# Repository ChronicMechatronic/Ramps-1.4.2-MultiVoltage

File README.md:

# Ramps-1.4.2-MultiVoltage

Special version of Ramps 1.4.2 allowing use of multiple power adapters to power a 3D printer.

Contains 5 seperate voltage rails for:
a 19.5V heated bed
a 12V hotend
one separate 12V stepper motor
two steppers running on 24V
one 5V stepper

The fifth stepper motor driver can be set to run off either the 5V, 12V, or 24V rail via 0 ohm links to be soldered on as necessary (add R30 for 5V; R29 for 12V; or R28 for 24V)
If you have a sufficiently powerful power supply the two 12V rails can be combined to run off a single barrel jack by populating R10 and R11 with 0 ohm links.

None of the voltage rails are constrained by anything other than the voltage rating of its capacitor, so repurpose as you please.

For pretty much everything else the standard documentation on https://reprap.org/wiki/RAMPS_1.4 applies

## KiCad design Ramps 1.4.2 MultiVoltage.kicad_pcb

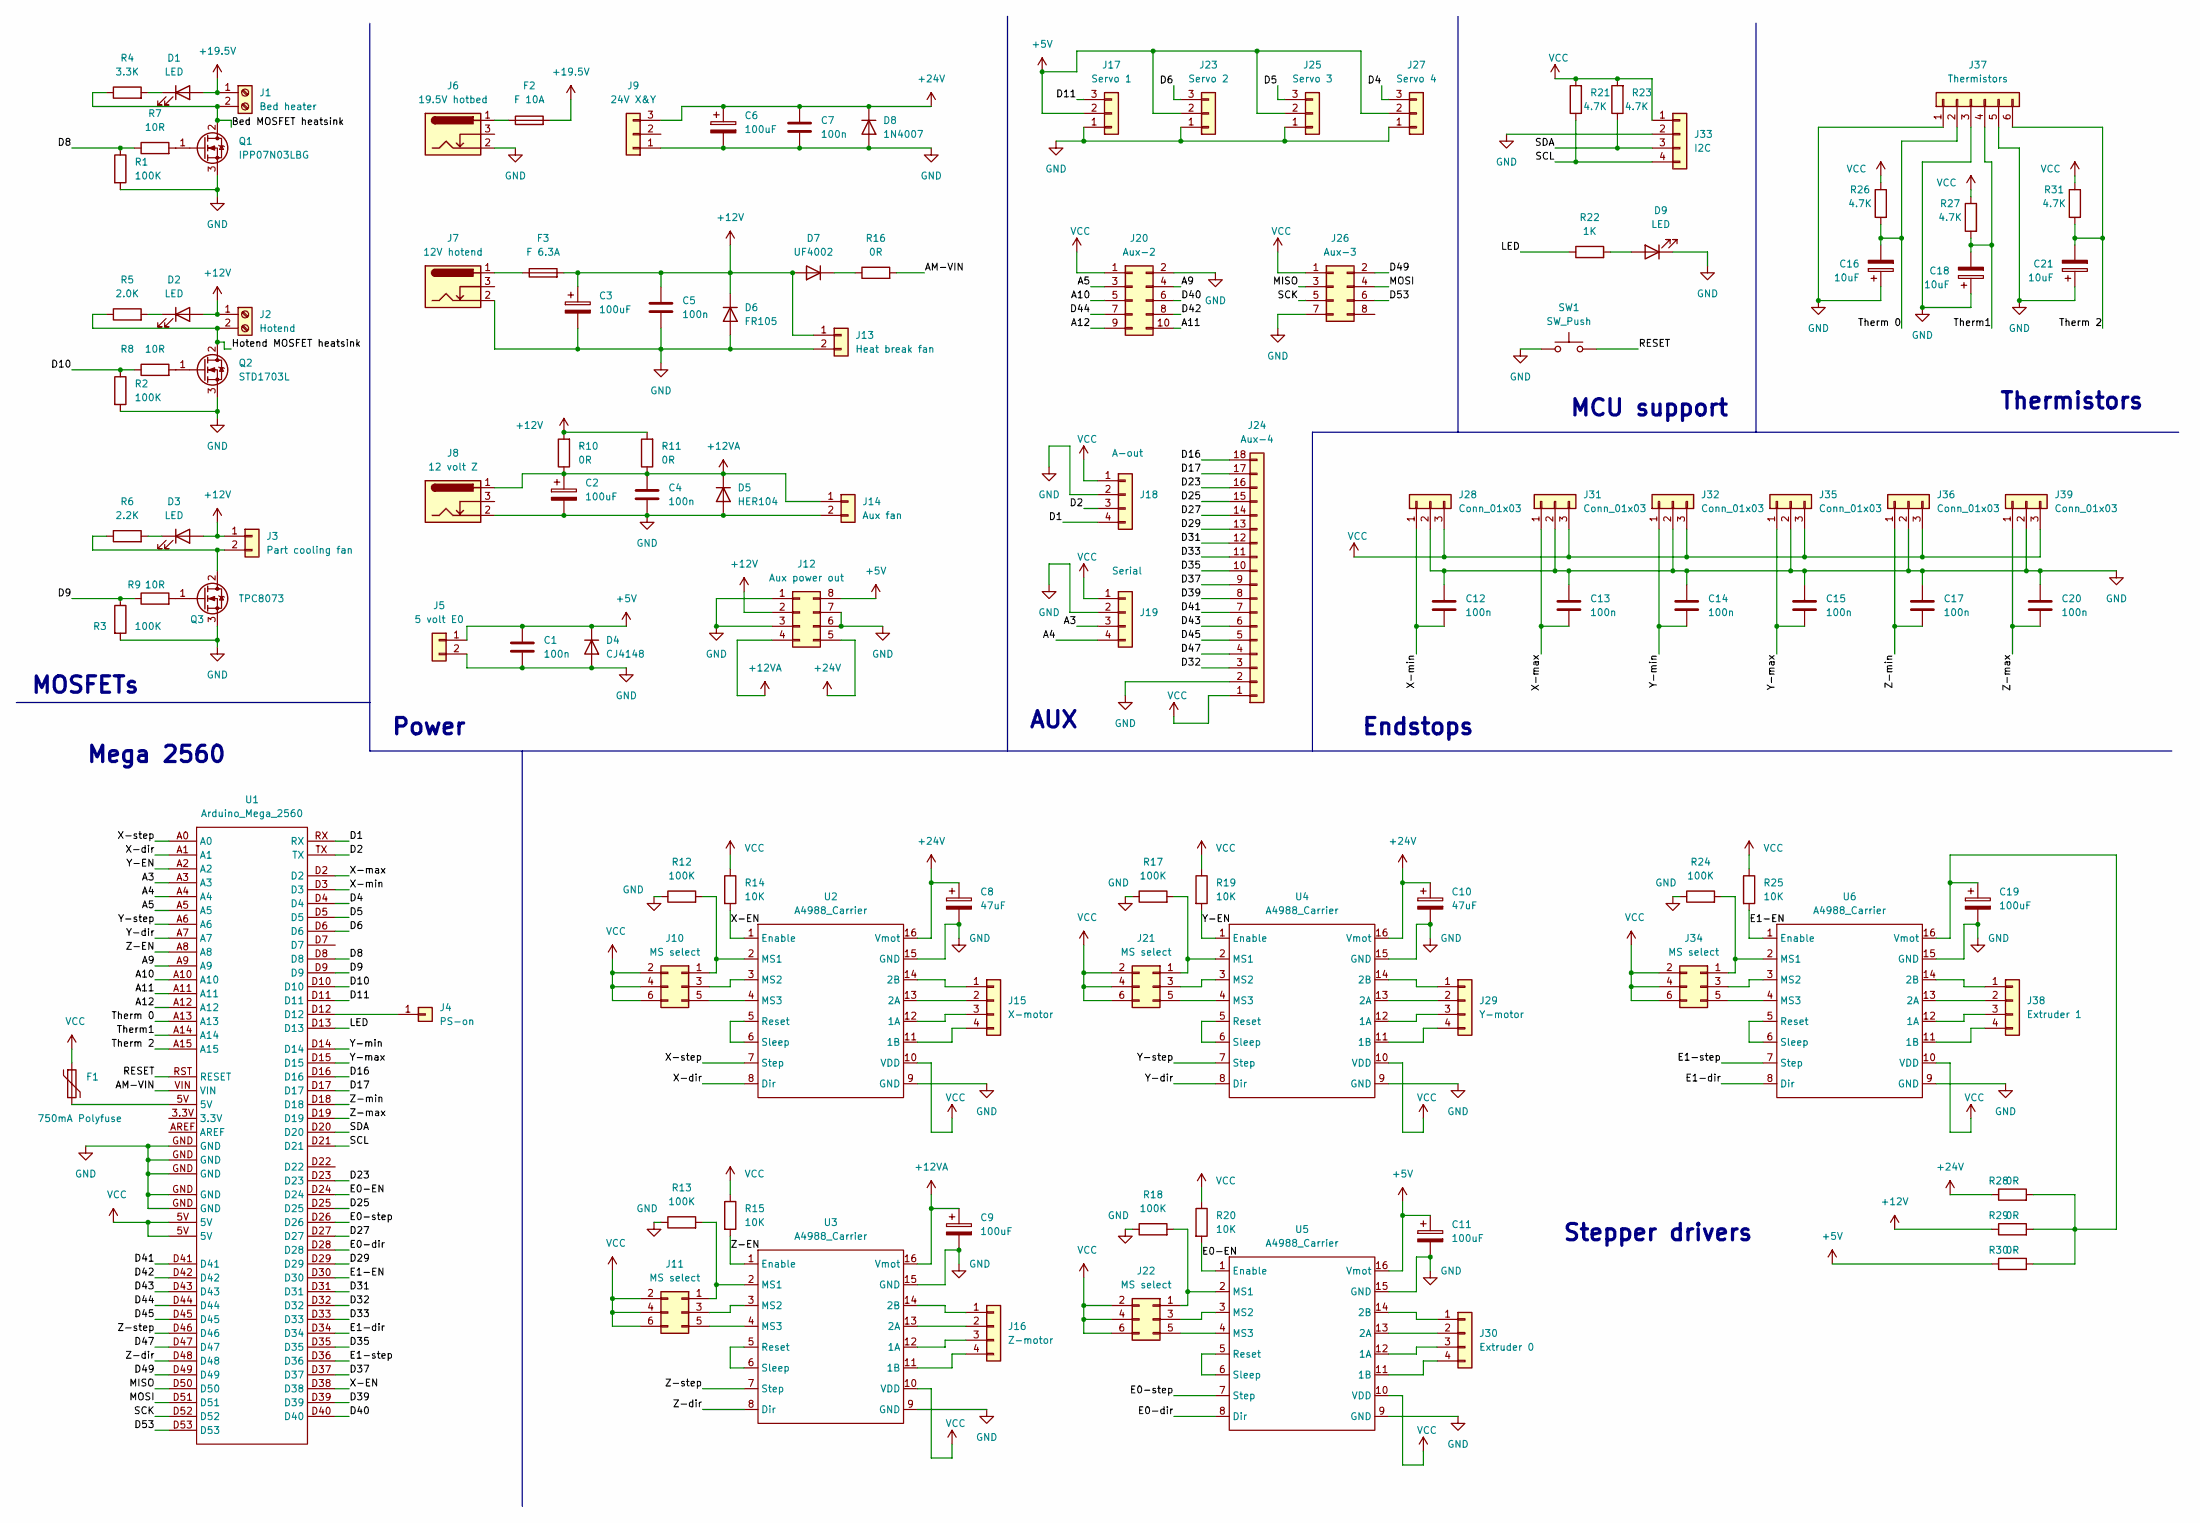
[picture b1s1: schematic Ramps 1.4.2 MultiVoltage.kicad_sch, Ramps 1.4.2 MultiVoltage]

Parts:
C1, C12, C13, C14, C15, C17, C20: 100n; C_0603_1608Metric
C2, C3, C9: 100uF; CP_Radial_D6.3mm_P2.50mm
C4, C5: 100n; C_0805_2012Metric
C6, C19: 100uF; CP_Radial_D8.0mm_P3.50mm
C7: 100n; C_1206_3216Metric
C8, C10: 47uF; CP_Radial_D8.0mm_P3.50mm
C11: 100uF; CP_Radial_D5.0mm_P2.50mm
C16, C18, C21: 10uF; CP_Radial_D4.0mm_P1.50mm
D1, D2, D3, D9: LED; LED_D5.0mm
D4: CJ4148; D_DO-35_SOD27_P7.62mm_Horizontal
D5: HER104; D_DO-41_SOD81_P2.54mm_Vertical_KathodeUp
D6: FR105; D_DO-41_SOD81_P2.54mm_Vertical_KathodeUp
D7: UF4002; D_DO-41_SOD81_P7.62mm_Horizontal
D8: 1N4007; D_DO-41_SOD81_P2.54mm_Vertical_AnodeUp
F1: 750mA Polyfuse; Fuse_Bourns_MF-RG400
F2: F 10A; Fuseholder_Cylinder-5x20mm_Stelvio-Kontek_PTF78_Horizontal_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
F3: F 6.3A; Standard 2-piece fuseholder
J1: Bed heater; TerminalBlock_Phoenix_MKDS-1,5-2_1x02_P5.00mm_Horizontal
J2: Hotend; TerminalBlock_Phoenix_MKDS-1,5-2_1x02_P5.00mm_Horizontal
J3: Part cooling fan; JST_XA_B02B-XASK-1_1x02_P2.50mm_Vertical
J4: PS-on; PinHeader_1x01_P2.54mm_Vertical
J5: 5 volt E0; JST_XH_S2B-XH-A-1_1x02_P2.50mm_Horizontal
J6: 19.5V hotbed; 5.5x2.5mm barrel jack connector square
J7: 12V hotend; BarrelJack_Horizontal
J8: 12 volt Z; BarrelJack_Horizontal
J9: 24V X&Y; JST_EH_S3B-EH_1x03_P2.50mm_Horizontal
J10, J11, J21, J22, J34: MS select; PinHeader_2x03_P2.54mm_Vertical
J12: Aux power out; PinHeader_2x04_P2.54mm_Vertical
J13: Heat break fan; JST_XA_B02B-XASK-1-A_1x02_P2.50mm_Vertical
J14: Aux fan; JST_XA_B02B-XASK-1-A_1x02_P2.50mm_Vertical
J15: X-motor; PinHeader_1x04_P2.54mm_Vertical
J16: Z-motor; PinHeader_1x04_P2.54mm_Vertical
J17: Servo 1; PinHeader_1x03_P2.54mm_Vertical
J18: A-out; PinHeader_1x04_P2.54mm_Vertical
J19: Serial; PinHeader_1x04_P2.54mm_Vertical
J20: Aux-2; PinHeader_2x05_P2.54mm_Vertical
J23: Servo 2; PinHeader_1x03_P2.54mm_Vertical
J24: Aux-4; PinHeader_1x18_P2.54mm_Vertical
J25: Servo 3; PinHeader_1x03_P2.54mm_Vertical
J26: Aux-3; PinHeader_2x04_P2.54mm_Vertical
J27: Servo 4; PinHeader_1x03_P2.54mm_Vertical
J28, J31, J32, J35, J36, J39: Conn_01x03; PinHeader_1x03_P2.54mm_Vertical
J29: Y-motor; PinHeader_1x04_P2.54mm_Vertical
J30: Extruder 0; PinHeader_1x04_P2.54mm_Vertical
J33: I2C; PinHeader_1x04_P2.54mm_Vertical
J37: Thermistors; PinHeader_1x06_P2.54mm_Vertical
J38: Extruder 1; PinHeader_1x04_P2.54mm_Vertical
Q1: IPP07N03LBG; TO-263-2
Q2: STD1703L; TO-252-2
Q3: TPC8073; TPC8073 MOSFET SOIC-8_4.5x5.08mm_P1.27mm
R1, R2, R3, R12, R13, R17, R18, R24: 100K; R_0603_1608Metric
R4: 3.3K; R_0805_2012Metric
R5: 2.0K; R_0805_2012Metric
R6: 2.2K; R_0805_2012Metric
R7, R8, R9: 10R; R_0603_1608Metric
R10, R11, R16, R28, R29, R30: 0R; R_1206_3216Metric
R14, R15, R19, R20, R25: 10K; R_0603_1608Metric
R21, R23, R26, R27, R31: 4.7K; R_0603_1608Metric
R22: 1K; R_0603_1608Metric
SW1: SW_Push; SW_Tactile_SPST_Angled_PTS645Vx39-2LFS
U1: Arduino_Mega_2560; Arduino Mega 252560 shield
U2, U3, U4, U5, U6: A4988_Carrier; A4988 carrier

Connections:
+5V: C1.1, C11.1, D4.1 (K), J5.1, J12.8, J17.2, J23.2, J25.2, J27.2, R30.1, U5.16 (Vmot)
+12V: C3.1, C5.1, D2.2 (A), D3.2 (A), D6.1 (K), D7.2 (A), F3.2, J2.1, J3.1, J12.2, J13.1, R10.2, R11.2, R29.1; also elsewhere on the board
+12VA: C2.1, C4.1, C9.1, D5.1 (K), J8.1, J12.4, J14.1, R10.1, R11.1, U3.16 (Vmot)
+19.5V: D1.2 (A), F2.2, J1.1
+24V: C6.1, C7.1, C8.1, C10.1, D8.1 (K), J9.3, J12.5, R28.1, U2.16 (Vmot), U4.16 (Vmot)
/A3: J19.3, U1.A3; also elsewhere on the board
/A4: J19.4, U1.A4; also elsewhere on the board
/A5: J20.3, U1.A5
/A9: J20.4, U1.A9
/A10: J20.5, U1.A10
/A11: J20.10, U1.A11
/A12: J20.9, U1.A12
/AM-VIN: R16.2, U1.VIN
/Bed MOSFET heatsink: J1.2, Q1.2 (D), R4.1
/D1: J18.4, U1.RX; also elsewhere on the board
/D2: J18.3, U1.TX; also elsewhere on the board
/D4: J27.3, U1.D4
/D5: J25.3, U1.D5
/D6: J23.3, U1.D6
/D8: R1.1, R7.1, U1.D8
/D9: R3.1, R9.1, U1.D9
/D10: R2.1, R8.1, U1.D10
/D11: J17.3, U1.D11
/D16: J24.18, U1.D16; also elsewhere on the board
/D17: J24.17, U1.D17; also elsewhere on the board
/D23: J24.16, U1.D23; also elsewhere on the board
/D25: J24.15, U1.D25; also elsewhere on the board
/D27: J24.14, U1.D27; also elsewhere on the board
/D29: J24.13, U1.D29; also elsewhere on the board
/D31: J24.12, U1.D31; also elsewhere on the board
/D32: J24.3, U1.D32; also elsewhere on the board
/D33: J24.11, U1.D33; also elsewhere on the board
/D35: J24.10, U1.D35; also elsewhere on the board
/D37: J24.9, U1.D37; also elsewhere on the board
/D39: J24.8, U1.D39; also elsewhere on the board
/D40: J20.6, U1.D40
/D41: J24.7, U1.D41; also elsewhere on the board
/D42: J20.8, U1.D42
/D43: J24.6, U1.D43; also elsewhere on the board
/D44: J20.7, U1.D44
/D45: J24.5, U1.D45; also elsewhere on the board
/D47: J24.4, U1.D47; also elsewhere on the board
/D49: J26.2, U1.D49
/D53: J26.6, U1.D53
/E0-EN: R20.2, U1.D24, U5.1 (Enable)
/E0-dir: U1.D28, U5.8 (Dir)
/E0-step: U1.D26, U5.7 (Step)
/E1-EN: R25.2, U1.D30, U6.1 (Enable)
/E1-dir: U1.D34, U6.8 (Dir)
/E1-step: U1.D36, U6.7 (Step)
/Hotend MOSFET heatsink: J2.2, Q2.2 (D), R5.1
/LED: R22.1, U1.D13
/MISO: J26.3, U1.D50
/MOSI: J26.4, U1.D51
/RESET: SW1.2, U1.RST (RESET)
/SCK: J26.5, U1.D52
/SCL: J33.4, R21.1, U1.D21
/SDA: J33.3, R23.1, U1.D20
/Therm1: C18.2, J37.4, R27.2, U1.A14
/Therm 0: C16.2, J37.2, R26.2, U1.A13
/Therm 2: C21.2, J37.6, R31.2, U1.A15
/X-EN: R14.2, U1.D38, U2.1 (Enable)
/X-dir: U1.A1, U2.8 (Dir)
/X-max: C13.2, J31.1, U1.D2
/X-min: C12.2, J28.1, U1.D3
/X-step: U1.A0, U2.7 (Step)
/Y-EN: R19.2, U1.A2, U4.1 (Enable)
/Y-dir: U1.A7, U4.8 (Dir)
/Y-max: C15.2, J35.1, U1.D15
/Y-min: C14.2, J32.1, U1.D14
/Y-step: U1.A6, U4.7 (Step)
/Z-EN: R15.2, U1.A8, U3.1 (Enable)
/Z-dir: U1.D48, U3.8 (Dir)
/Z-max: C20.2, J39.1, U1.D19
/Z-min: C17.2, J36.1, U1.D18
/Z-step: U1.D46, U3.7 (Step)
GND: C1.2, C2.2, C3.2, C4.2, C5.2, C6.2, C7.2, C8.2, C9.2, C10.2, C11.2, C12.1, C13.1, C14.1, C15.1, C16.1, C17.1, C18.1, C19.2, C20.1, C21.1, D4.2 (A), D5.2 (A), D6.2 (A), D8.2 (A), D9.1 (K), J5.2, J6.2, J7.2, J8.2, J9.1, J12.1, J12.3, J12.6, J12.7, J13.2, J14.2, J17.1, J18.2, J19.2, J20.2, J23.1, J24.2, J25.1, J26.7, J27.1, J28.2, J31.2, J32.2, J33.2, J35.2, J36.2, J37.1, J37.3, J37.5, J39.2, Q1.3 (S), Q2.3 (S), Q3.3 (S), R1.2, R2.2, R3.2, R12.1, R13.1, R17.1, R18.1, R24.1, SW1.1, U1.GND, U2.9 (GND), U2.15 (GND), U3.9 (GND), U3.15 (GND), U4.9 (GND), U4.15 (GND), U5.9 (GND), U5.15 (GND), U6.9 (GND), U6.15 (GND); also elsewhere on the board
unnamed: C19.1, R28.2, R29.2, R30.2, U6.16 (Vmot)
unnamed: D1.1 (K), R4.2
unnamed: D2.1 (K), R5.2
unnamed: D3.1 (K), R6.2
unnamed: D7.1 (K), R16.1
unnamed: D9.2 (A), R22.2
unnamed: F2.1, J6.1
unnamed: F3.1, J7.1
unnamed 85: J3.2, Q3.2 (D), R6.1; also elsewhere on the board
unnamed: J4.1, U1.D12
unnamed: J10.1, R12.2, U2.2 (MS1)
unnamed: J10.3, U2.3 (MS2)
unnamed: J10.5, U2.4 (MS3)
unnamed: J11.1, R13.2, U3.2 (MS1)
unnamed: J11.3, U3.3 (MS2)
unnamed: J11.5, U3.4 (MS3)
unnamed: J15.1, U2.14 (2B)
unnamed: J15.2, U2.13 (2A)
unnamed: J15.3, U2.12 (1A)
unnamed: J15.4, U2.11 (1B)
unnamed: J16.1, U3.14 (2B)
unnamed: J16.2, U3.13 (2A)
unnamed: J16.3, U3.12 (1A)
unnamed: J16.4, U3.11 (1B)
unnamed: J21.1, R17.2, U4.2 (MS1)
unnamed: J21.3, U4.3 (MS2)
unnamed: J21.5, U4.4 (MS3)
unnamed: J22.1, R18.2, U5.2 (MS1)
unnamed: J22.3, U5.3 (MS2)
unnamed: J22.5, U5.4 (MS3)
unnamed: J29.1, U4.14 (2B)
unnamed: J29.2, U4.13 (2A)
unnamed: J29.3, U4.12 (1A)
unnamed: J29.4, U4.11 (1B)
unnamed: J30.1, U5.14 (2B)
unnamed: J30.2, U5.13 (2A)
unnamed: J30.3, U5.12 (1A)
unnamed: J30.4, U5.11 (1B)
unnamed: J34.1, R24.2, U6.2 (MS1)
unnamed: J34.3, U6.3 (MS2)
unnamed: J34.5, U6.4 (MS3)
unnamed: J38.1, U6.14 (2B)
unnamed: J38.2, U6.13 (2A)
unnamed: J38.3, U6.12 (1A)
unnamed: J38.4, U6.11 (1B)
unnamed: Q1.1 (G), R7.2
unnamed: Q2.1 (G), R8.2
unnamed: Q3.1 (G), R9.2
unnamed: U2.5 (Reset), U2.6 (Sleep)
unnamed: U3.5 (Reset), U3.6 (Sleep)
unnamed: U4.5 (Reset), U4.6 (Sleep)
unnamed: U5.5 (Reset), U5.6 (Sleep)
unnamed: U6.5 (Reset), U6.6 (Sleep)

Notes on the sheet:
AUX
MOSFETs
Mega 2560
Power
Endstops
MCU support
Thermistors
Stepper drivers

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
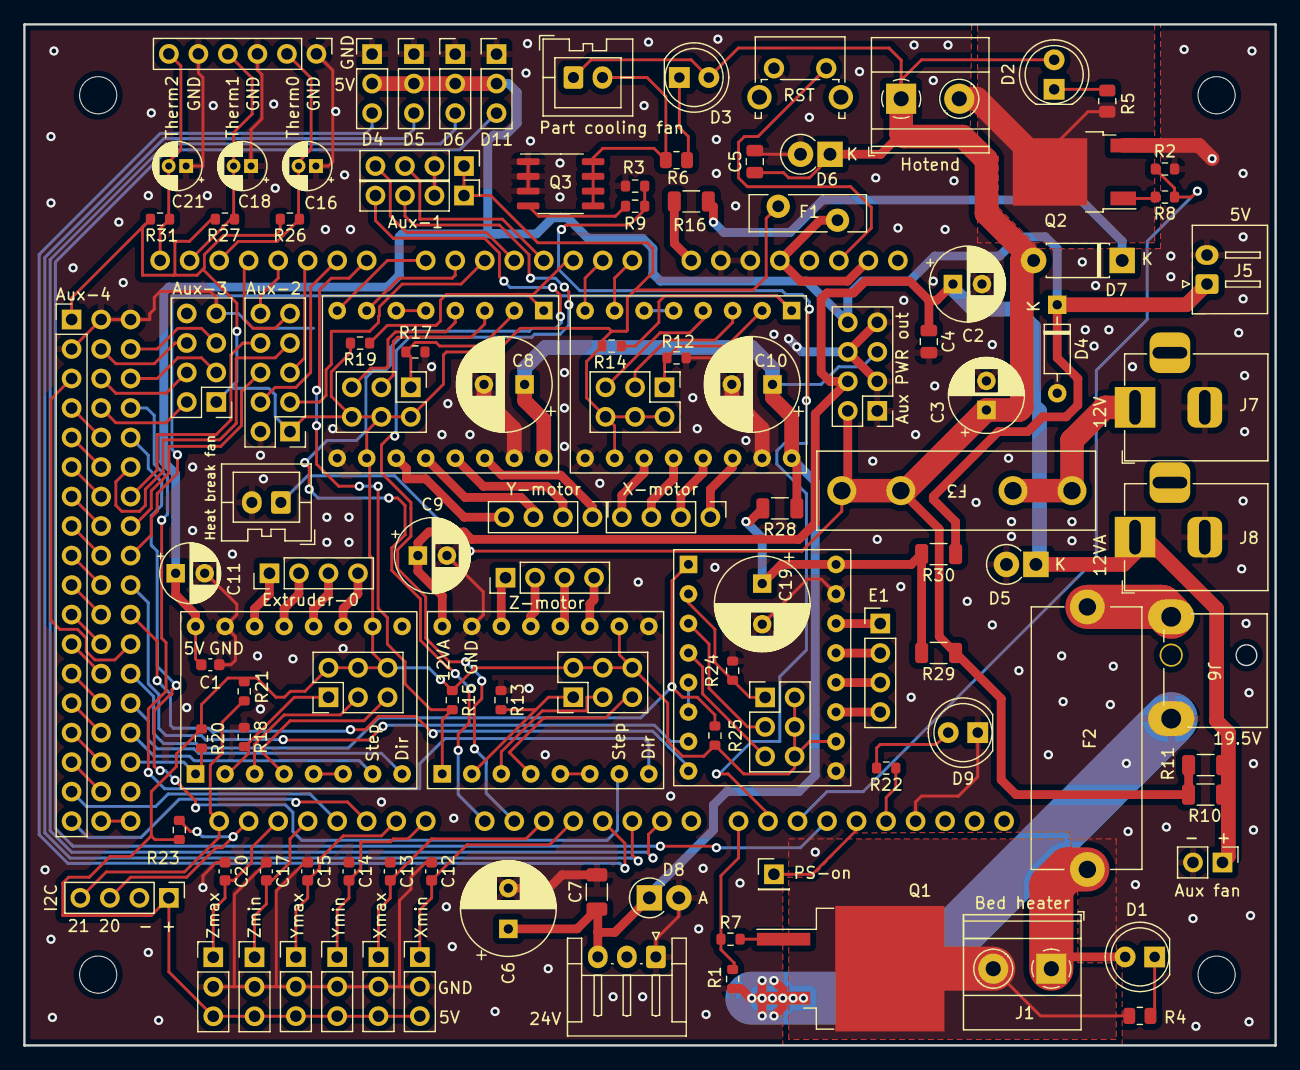
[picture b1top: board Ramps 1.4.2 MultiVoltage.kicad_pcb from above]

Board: 2 copper layers, 107.7 x 87.9 mm, 117 parts (0 on the bottom side), 132 nets.

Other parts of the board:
Aux-1: A-out; PinHeader_1x04_P2.54mm_Vertical
Aux-4: Aux-4; PinHeader_1x18_P2.54mm_Vertical
Part cooling fan: Part cooling fan; JST_XA_B02B-XASK-1_1x02_P2.50mm_Vertical
REF1, REF2, REF3, REF4: MountingHole_3.2mm_M3
SRL: Serial; PinHeader_1x04_P2.54mm_Vertical

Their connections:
+12V: Part cooling fan.1; also elsewhere on the board
/A3: SRL.3; also elsewhere on the board
/A4: SRL.4; also elsewhere on the board
/D1: Aux-1.4; also elsewhere on the board
/D2: Aux-1.3; also elsewhere on the board
/D16: Aux-4.18; also elsewhere on the board
/D17: Aux-4.17; also elsewhere on the board
/D23: Aux-4.16; also elsewhere on the board
/D25: Aux-4.15; also elsewhere on the board
/D27: Aux-4.14; also elsewhere on the board
/D29: Aux-4.13; also elsewhere on the board
/D31: Aux-4.12; also elsewhere on the board
/D32: Aux-4.3; also elsewhere on the board
/D33: Aux-4.11; also elsewhere on the board
/D35: Aux-4.10; also elsewhere on the board
/D37: Aux-4.9; also elsewhere on the board
/D39: Aux-4.8; also elsewhere on the board
/D41: Aux-4.7; also elsewhere on the board
/D43: Aux-4.6; also elsewhere on the board
/D45: Aux-4.5; also elsewhere on the board
/D47: Aux-4.4; also elsewhere on the board
GND: Aux-1.2, Aux-4.2, SRL.2; also elsewhere on the board
unnamed 85: Part cooling fan.2; also elsewhere on the board
